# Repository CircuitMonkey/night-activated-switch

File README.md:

# night-activated-switch
A simple switch PCB that activates when light is below a threshold.

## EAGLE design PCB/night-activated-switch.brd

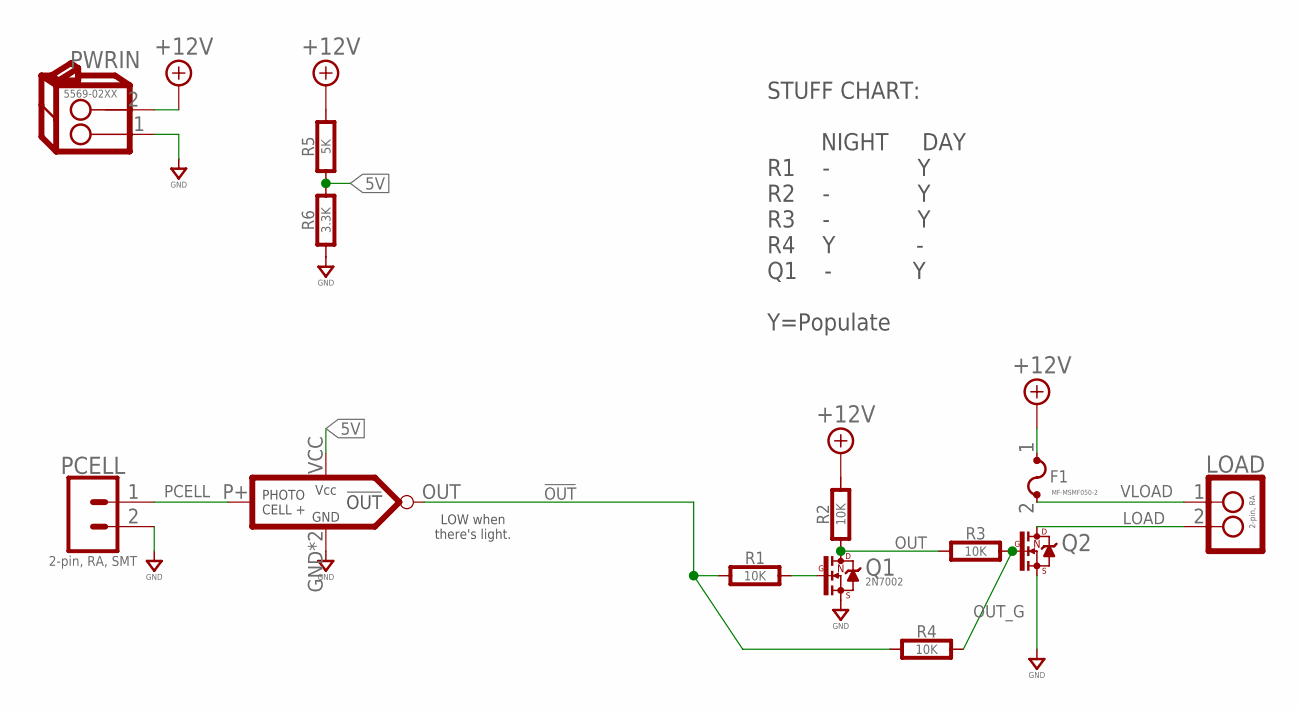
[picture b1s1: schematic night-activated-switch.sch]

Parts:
F1: MF-MSMF050-2; BOURNS-MF-MSMF
LOAD: 2-pin, RA; MOLEX-105313-XX02
LS1: Light Sensor; LIGHT-SENSOR-MODULE-B07QKJPWCG
PCELL: 2-pin, RA, SMT; S2B-PH-SM4-
PWRIN: 5569-02XX; MOLEX-5569-02XX
Q1: 2N7002; SOT-23
Q2: N-FET_SI2318A; SOT-23
R1, R2, R3, R4: 10K; 0603-RES
R5: 5K; 0603-RES
R6: 3.3K; 0603-RES

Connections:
5V: LS1.VCC, R5.2, R6.1
!OUT: LS1.OUT, R1.1, R4.1
+12V: F1.1, PWRIN.2, R2.1, R5.1
GND: LS1.GND, LS1.P- (GND), PCELL.2, PWRIN.1, Q1.2 (S), Q2.2 (S), R6.2
LOAD: LOAD.2, Q2.3 (D)
unnamed: Q1.1 (G), R1.2
OUT: Q1.3 (D), R2.2, R3.1
OUT_G: Q2.1 (G), R3.2, R4.2
PCELL: LS1.P+ (CELL), PCELL.1
VLOAD: F1.2, LOAD.1

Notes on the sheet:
LOW when there's light.
STUFF CHART: NIGHT DAY R1 - Y R2 - Y R3 - Y R4 Y - Q1 - Y Y=Populate

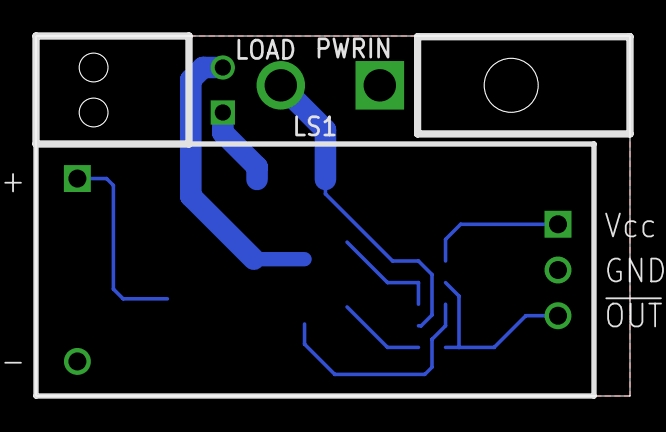
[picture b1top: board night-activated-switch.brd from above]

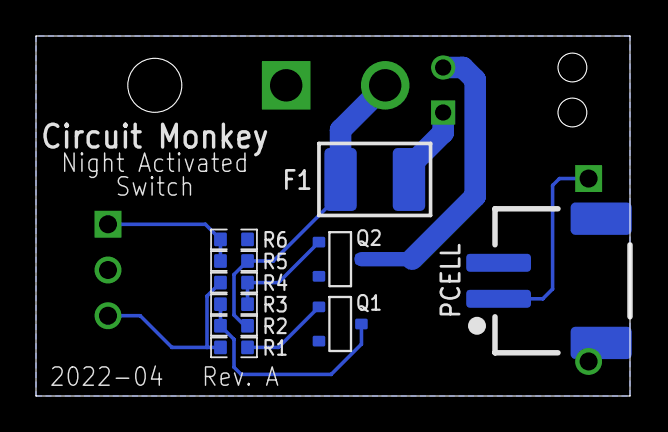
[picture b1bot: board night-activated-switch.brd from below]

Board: 2 copper layers, 33.0 x 20.0 mm, 13 parts (10 on the bottom side), 10 nets.

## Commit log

2022-04-12 Rev A
2022-04-12 Added Rev. A to silk
2022-04-13 Update BOM
2022-05-17 Update voltage divider values.
